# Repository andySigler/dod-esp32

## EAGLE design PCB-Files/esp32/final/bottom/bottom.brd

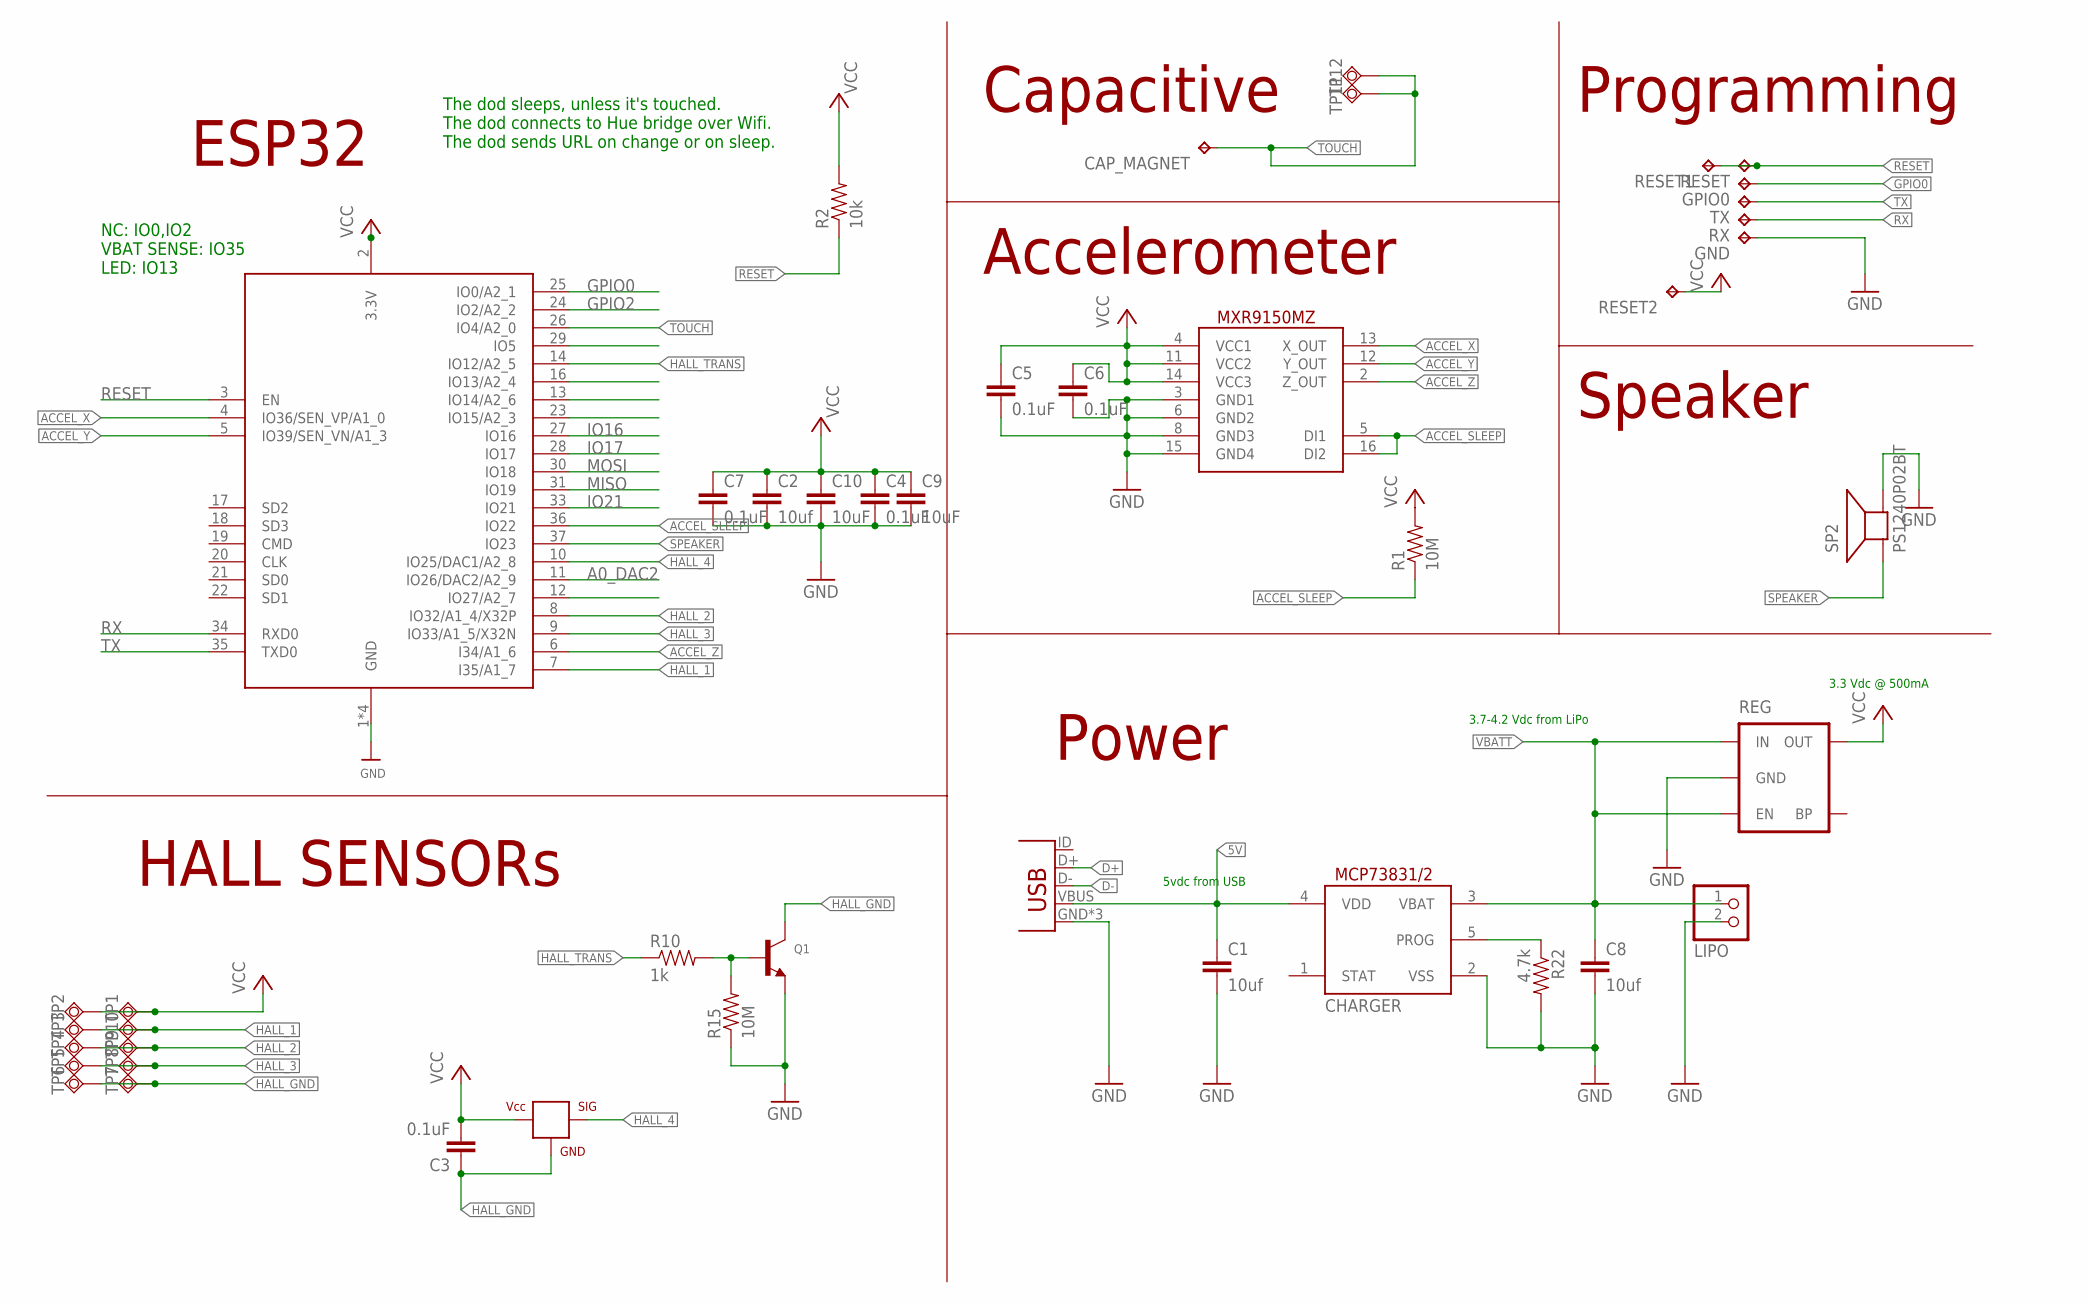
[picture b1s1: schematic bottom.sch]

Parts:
C1, C8: 10uf; 0603-CAP
C2: 10uf; 0402-CAP
C3: 0.1uF; 0603-CAP
C4, C5, C6, C7: 0.1uF; 0402-CAP
C9, C10: 10uF; 0402-CAP
CAP_MAGNET: TPTP10R; TP10R
CHARGER: MCP73831/OT; SOT23-5L
GND: TPTP13SQ; TP13SQ
GPIO0: TPTP13R; TP13R
HALL: A1304; SOT23-3
JP1: USB-MICROB
LIPO: JST_2PIN-THM; JST-PH-2-THM
Q1: TRANSISTOR_NPN; SOT-23-R
R1, R15: 10M; 0402-RES
R2: 10k; 0402-RES
R10: 1k; 0402-RES
R22: 4.7k; 0402-RES
REG: MIC52053.3V; SOT23-5
RESET, RESET1, RESET2: TPTP13R; TP13R
RX: TPTP13R; TP13R
SP2: PS1240P02BT; PS12
TP1, TP2, TP3, TP4, TP5, TP6, TP7, TP8, TP9, TP10, TP11, TP12: TPSQTP10SQ; TP10SQ
TX: TPTP13R; TP13R
U$1: ACCELEROMETER_MXR9150MZ; MXR9150MZ
X2: ESP32_WROOM32_SKINNY; WROOM32_SKINNY

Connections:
5V: C1.1, CHARGER.4 (VDD), JP1.VBUS
A0_DAC2: X2.11 (IO26/DAC2/A2_9)
ACCEL_SLEEP: R1.1, U$1.5 (DI1), U$1.16 (DI2), X2.36 (IO22)
ACCEL_X: U$1.13 (X_OUT), X2.4 (IO36/SEN_VP/A1_0)
ACCEL_Y: U$1.12 (Y_OUT), X2.5 (IO39/SEN_VN/A1_3)
ACCEL_Z: U$1.2 (Z_OUT), X2.6 (I34/A1_6)
D+: JP1.D+
D-: JP1.D-
GND: C1.2, C2.2, C4.2, C5.2, C6.2, C7.2, C8.2, C9.2, C10.2, CHARGER.2 (VSS), GND.TP, JP1.GND, JP1.MT1 (GND), JP1.MT2 (GND), LIPO.2 (1), Q1.3-EMITTER (E), R15.1, R22.2, REG.2 (GND), SP2.P$2 (-), U$1.3 (GND1), U$1.6 (GND2), U$1.8 (GND3), U$1.15 (GND4), X2.1 (GND), X2.15 (GND), X2.38 (GND), X2.P$1 (GND)
GPIO0: GPIO0.TP, X2.25 (IO0/A2_1)
GPIO2: X2.24 (IO2/A2_2)
HALL_1: TP3.TP, TP10.TP, X2.7 (I35/A1_7)
HALL_2: TP4.TP, TP9.TP, X2.8 (IO32/A1_4/X32P)
HALL_3: TP5.TP, TP8.TP, X2.9 (IO33/A1_5/X32N)
HALL_4: HALL.2 (SIG), X2.10 (IO25/DAC1/A2_8)
HALL_GND: C3.1, HALL.3 (GND), Q1.2-COLLECTOR (C), TP6.TP, TP7.TP
HALL_TRANS: R10.1, X2.14 (IO12/A2_5)
IO13_A12: X2.16 (IO13/A2_4)
IO14_A6: X2.13 (IO14/A2_6)
IO15_A8: X2.23 (IO15/A2_3)
IO16: X2.27 (IO16)
IO17: X2.28 (IO17)
IO21: X2.33 (IO21)
IO27_A10: X2.12 (IO27/A2_7)
MISO: X2.31 (IO19)
MOSI: X2.30 (IO18)
unnamed: CHARGER.5 (PROG), R22.1
unnamed: Q1.1-BASE (B), R10.2, R15.2
RESET: R2.1, RESET.TP, RESET1.TP, X2.3 (EN)
RX: RX.TP, X2.34 (RXD0)
SPEAKER: SP2.P$1 (+), X2.37 (IO23)
TOUCH: CAP_MAGNET.TP, TP11.TP, TP12.TP, X2.26 (IO4/A2_0)
TX: TX.TP, X2.35 (TXD0)
VBATT: C8.1, CHARGER.3 (VBAT), LIPO.1 (2), REG.1 (IN), REG.3 (EN)
VCC: C2.1, C3.2, C4.1, C5.1, C6.1, C7.1, C9.1, C10.1, HALL.1 (VCC), R1.2, R2.2, REG.5 (OUT), RESET2.TP, TP1.TP, TP2.TP, U$1.4 (VCC1), U$1.11 (VCC2), U$1.14 (VCC3), X2.2 (3.3V)

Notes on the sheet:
ESP32
NC: IO0,IO2 VBAT SENSE: IO35 LED: IO13
The dod sleeps, unless it's touched. The dod connects to Hue bridge over Wifi. The dod sends URL on change or on sleep.
HALL SENSORs
Programming
Power
5vdc from USB
3.7-4.2 Vdc from LiPo
3.3 Vdc @ 500mA
Capacitive
Accelerometer
Speaker

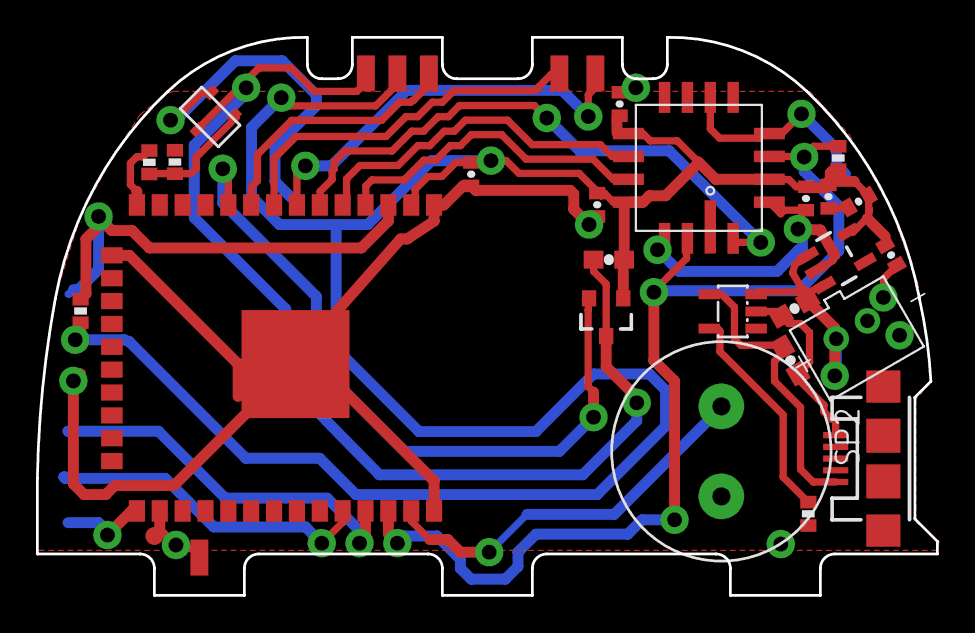
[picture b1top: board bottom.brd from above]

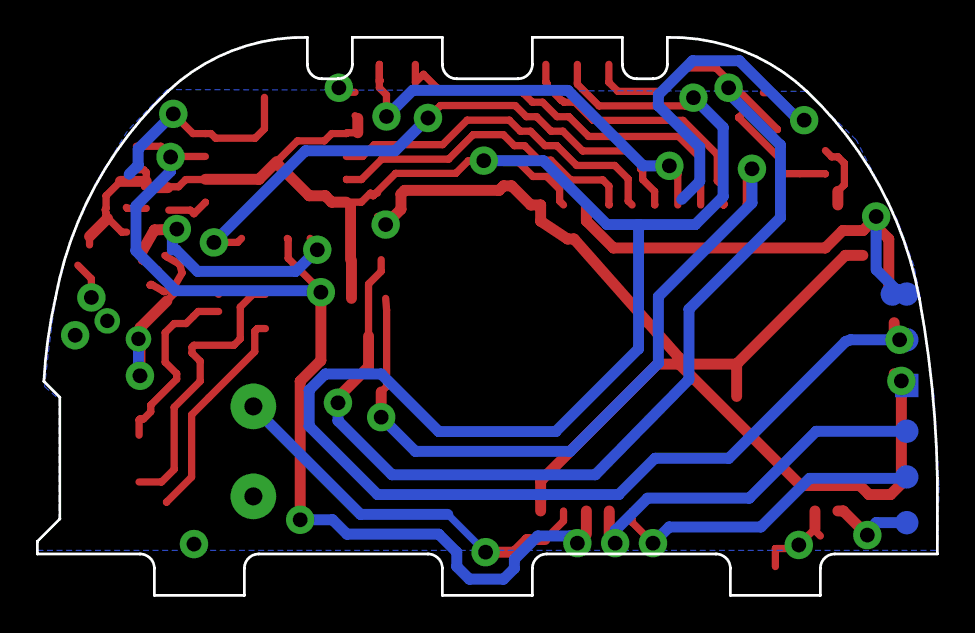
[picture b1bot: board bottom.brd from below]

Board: 2 copper layers, 50.0 x 31.0 mm, 44 parts (7 on the bottom side), 22 nets.

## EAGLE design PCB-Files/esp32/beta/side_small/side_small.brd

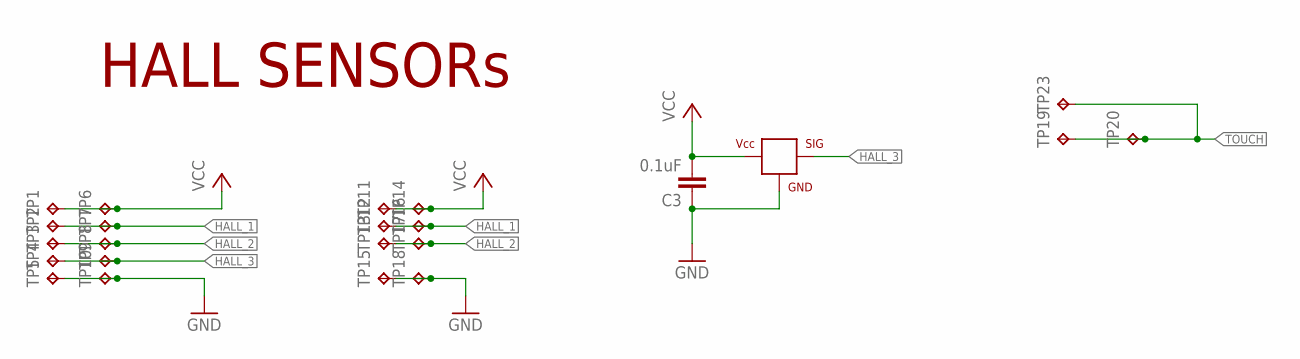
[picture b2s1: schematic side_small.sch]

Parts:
C3: 0.1uF; 0603-CAP
HALL: HALLEFFECT-A1326; SOT23-3
TP1, TP2, TP3, TP4, TP5, TP6, TP7, TP8, TP9, TP10, TP11, TP12, TP13, TP14, TP15, TP16, TP17, TP18, TP19, TP20, TP23: TPTP10SQ; TP10SQ

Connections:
GND: C3.1, HALL.3 (GND), TP5.TP, TP10.TP, TP15.TP, TP18.TP
HALL_1: TP2.TP, TP7.TP, TP12.TP, TP16.TP
HALL_2: TP3.TP, TP8.TP, TP13.TP, TP17.TP
HALL_3: HALL.2 (SIG), TP4.TP, TP9.TP
TOUCH: TP19.TP, TP20.TP, TP23.TP
VCC: C3.2, HALL.1 (VCC), TP1.TP, TP6.TP, TP11.TP, TP14.TP

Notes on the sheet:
HALL SENSORs

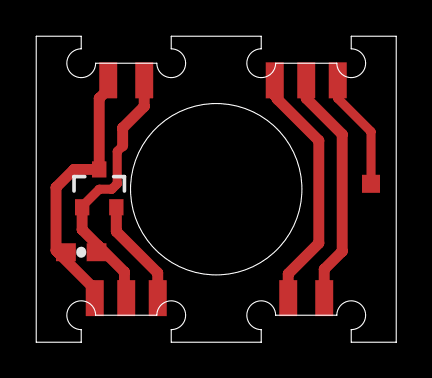
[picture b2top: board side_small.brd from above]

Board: 2 copper layers, 20.0 x 17.0 mm, 23 parts (0 on the bottom side), 6 nets.

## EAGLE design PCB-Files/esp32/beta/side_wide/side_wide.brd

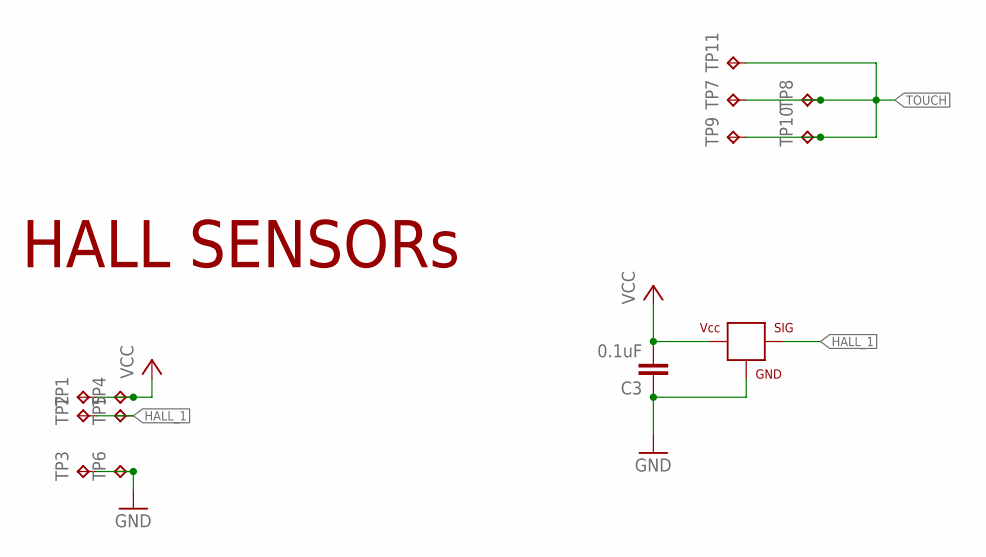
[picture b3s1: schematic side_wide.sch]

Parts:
C3: 0.1uF; 0603-CAP
HALL: HALLEFFECT-A1326; SOT23-3
TP1, TP2, TP3, TP4, TP5, TP6, TP7, TP8, TP9, TP10, TP11: TPTP10SQ; TP10SQ

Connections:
GND: C3.1, HALL.3 (GND), TP3.TP, TP6.TP
HALL_1: HALL.2 (SIG), TP2.TP, TP5.TP
TOUCH: TP7.TP, TP8.TP, TP9.TP, TP10.TP, TP11.TP
VCC: C3.2, HALL.1 (VCC), TP1.TP, TP4.TP

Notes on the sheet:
HALL SENSORs

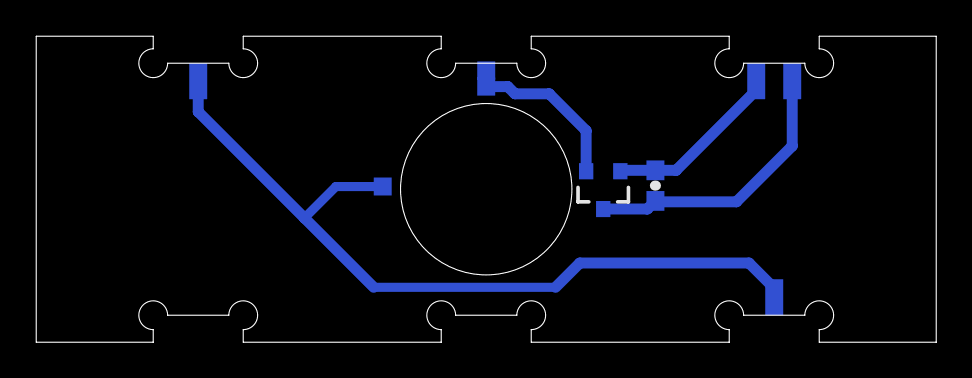
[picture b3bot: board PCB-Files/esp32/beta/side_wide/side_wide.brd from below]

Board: 2 copper layers, 50.0 x 17.0 mm, 13 parts (13 on the bottom side), 4 nets.

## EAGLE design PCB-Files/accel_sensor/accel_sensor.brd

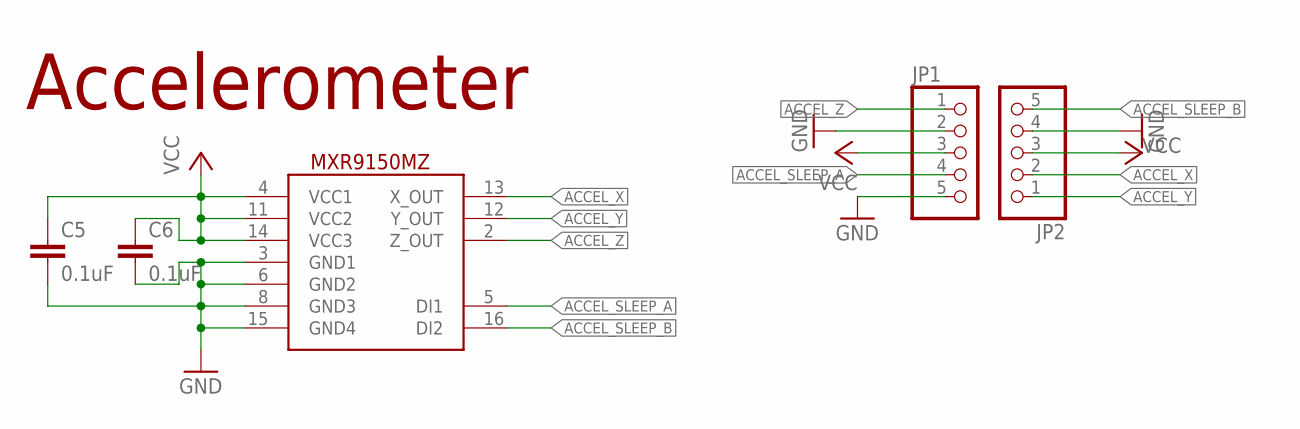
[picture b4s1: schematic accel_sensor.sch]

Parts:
C5, C6: 0.1uF; 0402-CAP
JP1, JP2: PINHD-1X5; 1X05
U$1: ACCELEROMETER_MXR9150MZ; MXR9150MZ

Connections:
ACCEL_SLEEP_A: JP1.4, U$1.5 (DI1)
ACCEL_SLEEP_B: JP2.5, U$1.16 (DI2)
ACCEL_X: JP2.2, U$1.13 (X_OUT)
ACCEL_Y: JP2.1, U$1.12 (Y_OUT)
ACCEL_Z: JP1.1, U$1.2 (Z_OUT)
GND: C5.2, C6.2, JP1.2, JP1.5, JP2.4, U$1.3 (GND1), U$1.6 (GND2), U$1.8 (GND3), U$1.15 (GND4)
VCC: C5.1, C6.1, JP1.3, JP2.3, U$1.4 (VCC1), U$1.11 (VCC2), U$1.14 (VCC3)

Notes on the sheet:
Accelerometer

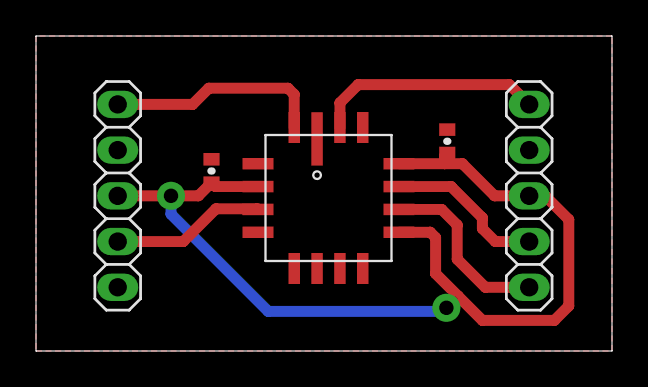
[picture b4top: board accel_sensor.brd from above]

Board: 2 copper layers, 32.0 x 17.5 mm, 5 parts (0 on the bottom side), 7 nets.

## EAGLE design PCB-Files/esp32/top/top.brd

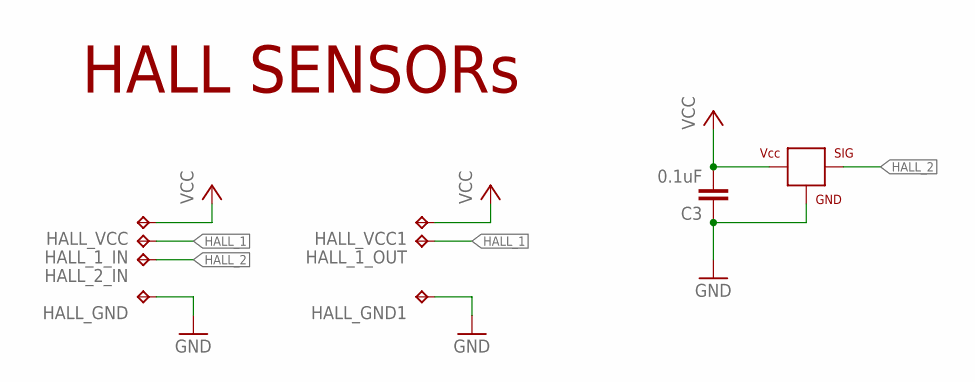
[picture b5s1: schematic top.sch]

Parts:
C3: 0.1uF; 0603-CAP
HALL: HALLEFFECT-A1326; SOT23-3
HALL_1_IN, HALL_1_OUT, HALL_2_IN: TPTP20SQ; TP20SQ
HALL_GND, HALL_GND1: TPTP20SQ; TP20SQ
HALL_VCC, HALL_VCC1: TPTP20SQ; TP20SQ

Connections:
GND: C3.1, HALL.3 (GND), HALL_GND.TP, HALL_GND1.TP
HALL_1: HALL_1_IN.TP, HALL_1_OUT.TP
HALL_2: HALL.2 (SIG), HALL_2_IN.TP
VCC: C3.2, HALL.1 (VCC), HALL_VCC.TP, HALL_VCC1.TP

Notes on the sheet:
HALL SENSORs

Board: 2 copper layers, 9 parts (9 on the bottom side), 4 nets, no tracks yet.

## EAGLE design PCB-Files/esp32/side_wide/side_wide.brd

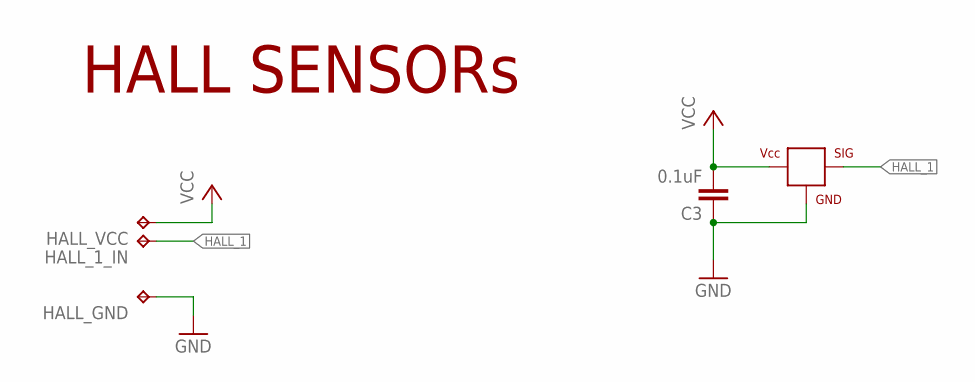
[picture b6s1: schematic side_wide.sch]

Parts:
C3: 0.1uF; 0603-CAP
HALL: HALLEFFECT-A1326; SOT23-3
HALL_1_IN: TPTP20SQ; TP20SQ
HALL_GND: TPTP20SQ; TP20SQ
HALL_VCC: TPTP20SQ; TP20SQ

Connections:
GND: C3.1, HALL.3 (GND), HALL_GND.TP
HALL_1: HALL.2 (SIG), HALL_1_IN.TP
VCC: C3.2, HALL.1 (VCC), HALL_VCC.TP

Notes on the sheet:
HALL SENSORs

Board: 2 copper layers, 5 parts (5 on the bottom side), 3 nets, no tracks yet.

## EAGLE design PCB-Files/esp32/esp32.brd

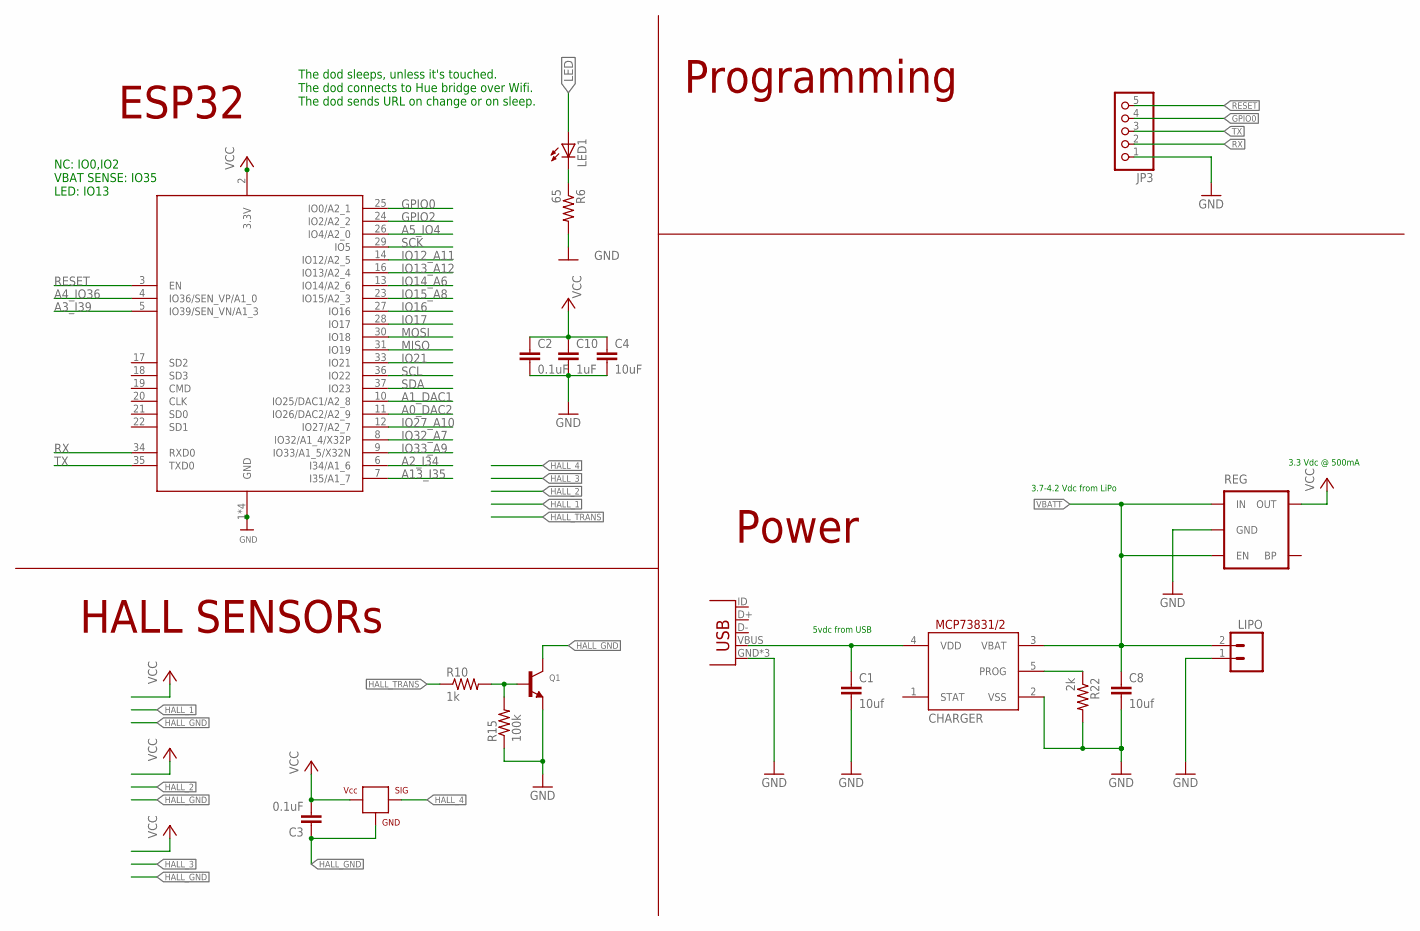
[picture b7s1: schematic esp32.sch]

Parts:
C1, C8: 10uf; 0603-CAP
C2: 0.1uF; 0402-CAP
C3: 0.1uF; 0603-CAP
C4: 10uF; 0402-CAP
C10: 1uF; 0402-CAP
CHARGER: MCP73831/OT; SOT23-5L
HALL: HALLEFFECT-A1326; SOT23-3
JP1: USB-MICROB
JP3: PINHD-1X55X2MM; 1_05X2MM
LED1: LEDCHIPLED_0603; CHIPLED_0603
LIPO: M02; 1X02_LONGPADS
Q1: TRANSISTOR_NPN; SOT-23-R
R6: 65; 0805
R10: 1k; 0402-RES
R15: 100k; 0402-RES
R22: 2k; 0402-RES
REG: MIC52053.3V; SOT23-5
X2: ESP32_WROOM32_SKINNY; WROOM32_SKINNY

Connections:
5V: C1.1, CHARGER.4 (VDD), JP1.VBUS
A0_DAC2: X2.11 (IO26/DAC2/A2_9)
A1_DAC1: X2.10 (IO25/DAC1/A2_8)
A2_I34: X2.6 (I34/A1_6)
A3_I39: X2.5 (IO39/SEN_VN/A1_3)
A4_IO36: X2.4 (IO36/SEN_VP/A1_0)
A5_IO4: X2.26 (IO4/A2_0)
A13_I35: X2.7 (I35/A1_7)
GND: C1.2, C2.2, C4.2, C8.2, C10.2, CHARGER.2 (VSS), JP1.GND, JP1.MT1 (GND), JP1.MT2 (GND), JP3.1, LIPO.1, Q1.3-EMITTER (E), R6.2, R15.1, R22.2, REG.2 (GND), X2.1 (GND), X2.15 (GND), X2.38 (GND), X2.P$1 (GND)
GPIO0: JP3.4, X2.25 (IO0/A2_1)
GPIO2: X2.24 (IO2/A2_2)
HALL_4: HALL.2 (SIG)
HALL_GND: C3.1, HALL.3 (GND), Q1.2-COLLECTOR (C)
HALL_TRANS: R10.1
IO12_A11: X2.14 (IO12/A2_5)
IO13_A12: X2.16 (IO13/A2_4)
IO14_A6: X2.13 (IO14/A2_6)
IO15_A8: X2.23 (IO15/A2_3)
IO16: X2.27 (IO16)
IO17: X2.28 (IO17)
IO21: X2.33 (IO21)
IO27_A10: X2.12 (IO27/A2_7)
IO32_A7: X2.8 (IO32/A1_4/X32P)
IO33_A9: X2.9 (IO33/A1_5/X32N)
LED: LED1.A
MISO: X2.31 (IO19)
MOSI: X2.30 (IO18)
unnamed: LED1.C, R6.1
unnamed: CHARGER.5 (PROG), R22.1
unnamed: Q1.1-BASE (B), R10.2, R15.2
RESET: JP3.5, X2.3 (EN)
RX: JP3.2, X2.34 (RXD0)
SCK: X2.29 (IO5)
SCL: X2.36 (IO22)
SDA: X2.37 (IO23)
TX: JP3.3, X2.35 (TXD0)
VBATT: C8.1, CHARGER.3 (VBAT), LIPO.2, REG.1 (IN), REG.3 (EN)
VCC: C2.1, C3.2, C4.1, C10.1, HALL.1 (VCC), REG.5 (OUT), X2.2 (3.3V)

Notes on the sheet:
ESP32
NC: IO0,IO2 VBAT SENSE: IO35 LED: IO13
The dod sleeps, unless it's touched. The dod connects to Hue bridge over Wifi. The dod sends URL on change or on sleep.
HALL SENSORs
Programming
Power
5vdc from USB
3.7-4.2 Vdc from LiPo
3.3 Vdc @ 500mA

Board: 2 copper layers, 19 parts (0 on the bottom side), 12 nets, no tracks yet.

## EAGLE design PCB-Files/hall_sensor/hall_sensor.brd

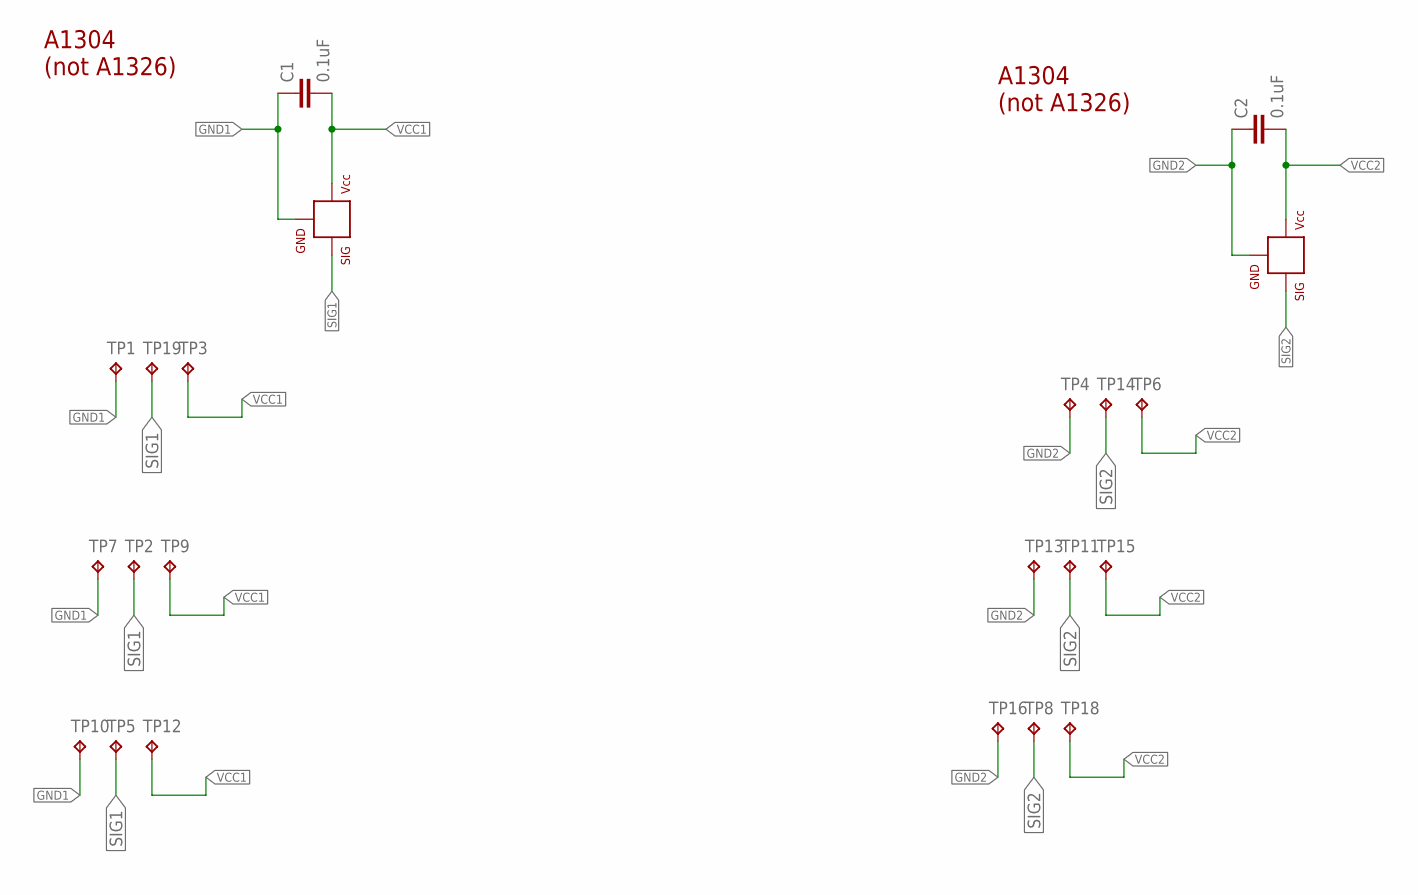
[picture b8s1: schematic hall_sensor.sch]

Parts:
C1, C2: 0.1uF; 0603-CAP
HALL, HALL1: HALLEFFECT-A1326; SOT23-3
TP1, TP3, TP4, TP6, TP7, TP9, TP10, TP12, TP13, TP15, TP16, TP18: TPTP10SQ; TP10SQ
TP2, TP5, TP8, TP11, TP14, TP19: TPTP15R; TP15R

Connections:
GND1: C1.1, HALL.3 (GND), TP1.TP, TP7.TP, TP10.TP
GND2: C2.1, HALL1.3 (GND), TP4.TP, TP13.TP, TP16.TP
SIG1: HALL.2 (SIG), TP2.TP, TP5.TP, TP19.TP
SIG2: HALL1.2 (SIG), TP8.TP, TP11.TP, TP14.TP
VCC1: C1.2, HALL.1 (VCC), TP3.TP, TP9.TP, TP12.TP
VCC2: C2.2, HALL1.1 (VCC), TP6.TP, TP15.TP, TP18.TP

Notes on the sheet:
A1304 (not A1326)

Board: 2 copper layers, 22 parts (11 on the bottom side), 6 nets, no tracks yet.

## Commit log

2017-11-27 init commit
2017-11-27 init board layout
2018-07-03 esp32 touch sketch tests
2019-02-03 rounded 4-side for class
2019-02-18 initial files for 4-sided PCBs; no routing done yet
2019-03-05 adds tone; lays out code skeleton
2019-03-05 basic layout; dimension for toothed joints
2019-03-06 shrink accel pads; accel-test pcb design
2019-03-07 all peripheral working on breadboard
2019-03-07 main PCB ready to mill for beta
2019-03-11 tests on beta pcb pass; includes wifi test in firmware
2019-03-11 creates final PCB version; revised beta side pcbs to match beta main pcb pinouts
2019-11-08 wifi creds

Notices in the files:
parts and their libraries:
SparkFun-Aesthetics: Licensing: Creative Commons ShareAlike 4.0 International - https://creativecommons.org/licenses/by-sa/4.0
microbuilder: This work is placed in the public domain, and may be freely used for commercial and non-commercial work with the following conditions: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
